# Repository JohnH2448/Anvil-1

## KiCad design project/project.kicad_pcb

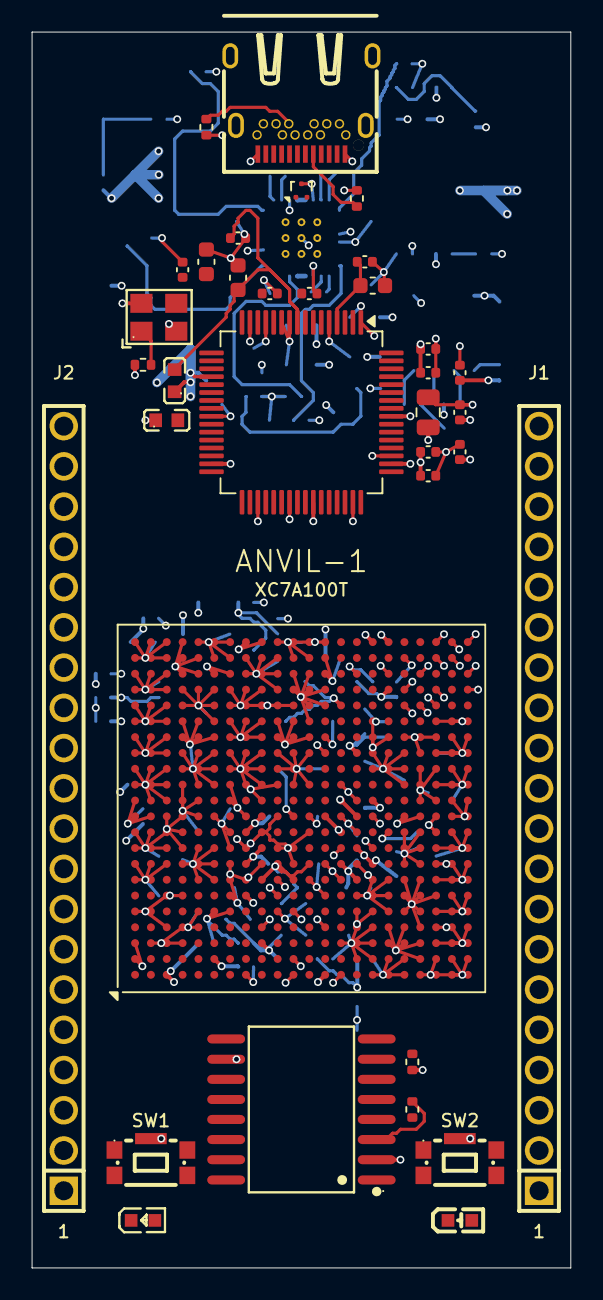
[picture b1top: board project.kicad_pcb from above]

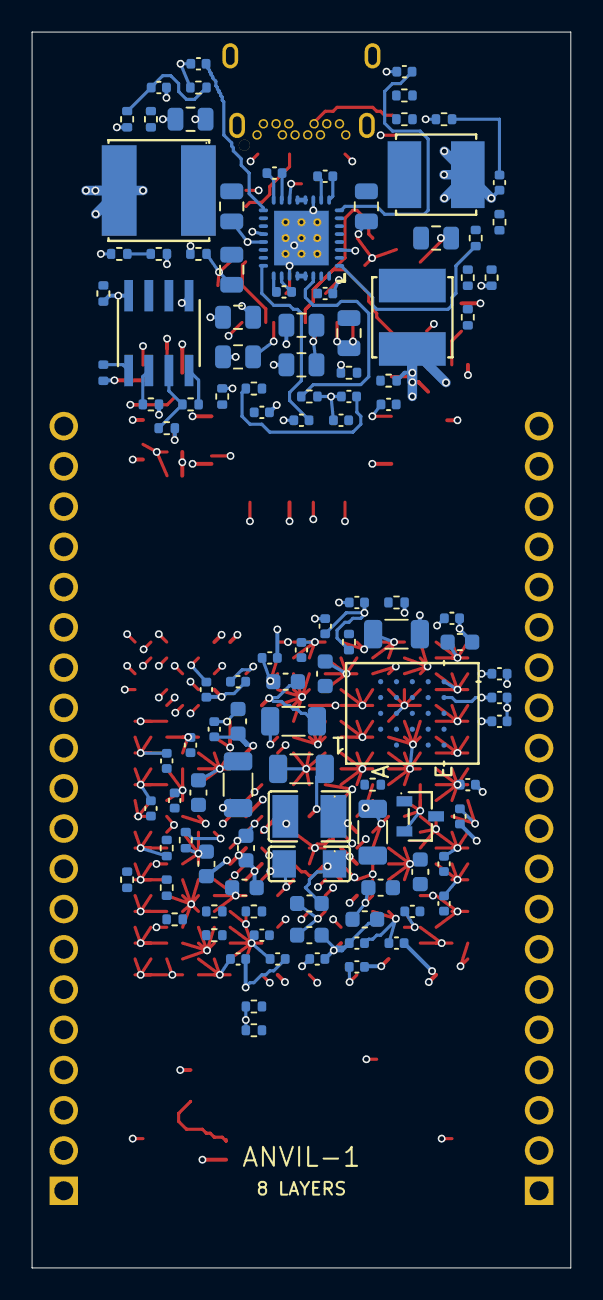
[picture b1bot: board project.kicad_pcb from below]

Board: 8 copper layers, 34.0 x 78.0 mm, 149 parts (114 on the bottom side), 120 nets.

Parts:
C1, C11, C16: 47nF; C_0402_1005Metric
C2, C3, C13, C15, C18, C20, C24: 22µF; C_0805_2012Metric
C4: 1.2nF; C_0402_1005Metric
C5, C14, C19: 22pF; C_0402_1005Metric
C6, C7, C8, C10: 10µF; C_0805_2012Metric
C9: 1µF; C_0402_1005Metric
C12, C17: 2.2nF; C_0402_1005Metric
C21, C22, C23, C27, C29, C31, C32, C33, C34, C35, C36, C37, C38, C39, C67, C76, C77, C78, C79: 100nF; C_0402_1005Metric
C25: 0.1µF; C_0402_1005Metric
C26: 3.3µF; C_0603_1608Metric
C28, C30, C41, C43, C44, C45, C46, C47, C58, C59, C65, C70, C72, C83, C85: 4.7µF; C_0603_1608Metric
C40: 330µF; C314600_C1210
C42, C48, C49, C50, C51, C52, C53, C54, C55, C60, C61, C62, C63, C64, C69, C73, C74, C75, C80, C81, C82, C84: 0.47µF; C_0402_1005Metric
C56: 0.47µF; C_1206_3216Metric
C57: 100µF; C15008_C1206
C66, C68, C71, C86: 47µF; C_1206_3216Metric
FB1, FB2: 600Ω@100MHz; C1002_L0603
J1, J2: 2.54mm 1*20P; C50981_HDR-TH_20P-P2_54-V-M-1
L1: 2.2µH; C160951_IND-SMD_L6_0-W6_0
L2, L3: 4.7µH; C162577_IND-SMD_L5_0-W5_0
LED1: GREEN; C2289_LED0603-RD
LED2: RED; C2286_LED-SMD_L1_6-W0_8-R-RD
OSC1: OT2EL89CJI-111YLC-12M; C5280582_OSC-SMD_4P-L3_2-W2_5-BL
Q1: AO3400A; C20917_SOT-23-3_L2_9-W1_3-P1_90-LS2_4-BR
R1, R7, R8, R11, R14, R19, R22, R25, R26, R27, R36, R39, R41, R42: 10kΩ; R_0402_1005Metric
R2: 12.4kΩ; R_0402_1005Metric
R3: 15kΩ; R_0402_1005Metric
R4: 73.2kΩ; R_0402_1005Metric
R5: 200kΩ; R_0402_1005Metric
R6: 67kΩ; R_0402_1005Metric
R9, R10: 20kΩ; R_0402_1005Metric
R12: 41.1kΩ; R_0402_1005Metric
R13: 45.3kΩ; R_0402_1005Metric
R15, R16, R17, R18: 100kΩ; R_0402_1005Metric
R20, R21: 5.1kΩ; R_0402_1005Metric
R23: 12kΩ; R_0402_1005Metric
R24, R40: 2.2kΩ; R_0402_1005Metric
R28, R29, R30, R31, R32, R34: 4.7kΩ; R_0402_1005Metric
R33, R37: 100Ω; R_0402_1005Metric
R35: 130Ω; R_0402_1005Metric
R38: 680Ω; R_0402_1005Metric
SW1, SW2: KMR221GLFS; C72443_KEY-SMD_KMR2XXGXXX
U1: XC7A100T-FGG484; BGA-484_23.0x23.0mm_Layout22x22_P1.0mm
U2: TPS65261RHBR; RHB0032E
U3: FT2232HL; LQFP-64_10x10mm_P0.5mm
U4: 93LC46B-E/SN; SOIC8-N_MC_MCH
U5: TPD2EUSB30; Texas_DRT-3
U6: W25Q256JVFIQT; C779876_SOIC-16_L10_3-W7_5-P1_27-LS10_3-BL
U7: IS66WVH16M8DALL-166B1LI; BGA24_IS66_ISI
USB1: USB-306F; C309341_USB-TYPE-C-TH_USB-306K

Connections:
/FPGA_CK_N: U1.E3, U7.B1
/FPGA_CK_P: U1.F3, U7.B2
/FPGA_CS: R41.2, U1.F1, U7.A3
/FPGA_RESET: R42.2, U1.K1, U7.A4
/FPGA_RWDS: R40.2, U1.H4, U7.C3
/FTDI_JTAG_TCK: U1.V12, U3.16
/FTDI_JTAG_TDI: U1.R13, U3.17
/FTDI_JTAG_TDO: U1.U13, U3.18
/FTDI_JTAG_TMS: U1.T13, U3.19
/OSC_12: OSC1.3, U1.W19, U3.2
/SPI_CLK: U1.L12, U6.16
/SPI_CS: R28.2, U1.T19, U6.7
/SPI_IO0: U1.P22, U6.15
/SPI_IO1: U1.R22, U6.8
/SPI_IO2: U1.P21, U6.9
/SPI_IO3: U1.R21, U6.1
/UART_RX: U1.R17, U3.38
/UART_TX: U1.N15, U3.39
/VBUS: C6.2, C7.2, C8.2, C9.2, R5.1, U2.12, U2.13, U2.28, U2.29, USB1.A4, USB1.A9, USB1.B4, USB1.B9
FTDI_VREGOUT: C26.1, C33.1, C34.1, C35.1, U3.12, U3.37, U3.49, U3.64
GND: C2.1, C3.1, C4.2, C6.1, C7.1, C8.1, C9.1, C10.1, C12.2, C13.1, C15.1, C17.2, C18.1, C20.1, C21.2, C22.2, C23.2, C24.2, C25.2, C26.2, C27.2, C28.2, C29.2, C30.2, C31.2, C32.2, C33.2, C34.2, C35.2, C36.2, C37.2, C38.2, C39.2, C40.2, C41.2, C42.2, C43.2, C44.2, C45.2, C46.2, C47.2, C48.2, C49.2, C50.2, C51.2, C52.2, C53.2, C54.2, C55.2, C56.2, C57.2, C58.2, C59.2, C60.2, C61.2, C62.2, C63.2, C64.2, C65.2, C66.2, C67.1, C68.2, C69.2, C70.2, C71.2, C72.2, C73.2, C74.2, C75.2, C76.2, C77.1, C78.1, C79.2, C80.2, C81.2, C82.2, C83.2, C84.2, C85.2, C86.2, J1.5, J1.10, J1.15, J1.20, J2.5, J2.10, J2.15, J2.20, OSC1.2, Q1.2, R3.2, R4.1, R6.1, R11.2, R14.2, R20.1, R21.2, R23.2, R30.1, R31.1, R33.2, R37.2, SW1.5, SW2.5, U1.A2, U1.A3, U1.A5, U1.A7, U1.A8, U1.A9, U1.A10, U1.A11, U1.A12, U1.A13, U1.A14, U1.A15, U1.A16, U1.A17, U1.A18, U1.A19, U1.A20, U1.A21, U1.A22, U1.AA1, U1.AA2, U1.AA3, U1.AA4, U1.AA5, U1.AA6, U1.AA7, U1.AA8, U1.AA9, U1.AA10, U1.AA11, U1.AA12, U1.AA13, U1.AA14, U1.AA15, U1.AA16, U1.AA17, U1.AA22, U1.AB1, U1.AB2, U1.AB3, U1.AB4, U1.AB5, U1.AB6, U1.AB7, U1.AB8, U1.AB9, U1.AB10, U1.AB11, U1.AB12, U1.AB13, U1.AB14, U1.AB15, U1.AB16, U1.AB17, U1.AB19, U1.B3, U1.B5, U1.B7, U1.B8, U1.B9, U1.B10, U1.B11, U1.B12, U1.B13, U1.B14, U1.B15, U1.B16, U1.B17, U1.B18, U1.B19, U1.B20, U1.B21, U1.B22, U1.C3, U1.C4, U1.C6, U1.C8, U1.C9, U1.C10, U1.C11, U1.C12, U1.C13, U1.C14, U1.C15, U1.C16, U1.C17, U1.C18, U1.C19, U1.C20, U1.C21, U1.C22, U1.D3, U1.D4, U1.D6, U1.D8, U1.D9, U1.D10, U1.D11, U1.D12, U1.D13, U1.D14, U1.D15, U1.D16, U1.D17, U1.D18, U1.D19, U1.D20, U1.D21, U1.D22, U1.E4, U1.E5, U1.E7, U1.E8, U1.E9, U1.E11, U1.E12, U1.E13, U1.E14, U1.E15, U1.E16, U1.E17, U1.E18, U1.E19, U1.E20, U1.E21, U1.E22, U1.F5, U1.F7, U1.F8, U1.F9, U1.F11, U1.F13, U1.F14, U1.F15, U1.F16, U1.F17, U1.F18, U1.F19, U1.F20, U1.F21, U1.F22, U1.G5, U1.G6, U1.G7, U1.G8, U1.G9, U1.G10, U1.G12, U1.G13, U1.G14, U1.G15, U1.G16, U1.G17, U1.G18, U1.G19, U1.G20, U1.G21, U1.G22, U1.H1, U1.H7, U1.H9, U1.H11, U1.H13, U1.H14, U1.H15, U1.H16, U1.H17, U1.H18, U1.H19, U1.H20, U1.H21, U1.H22, U1.J8, U1.J10, U1.J12, U1.J13, U1.J14, U1.J15, U1.J16, U1.J17, U1.J18, U1.J19, U1.J20, U1.J21, U1.J22, U1.K5, U1.K7, U1.K9, U1.K11, U1.K13, U1.K14, U1.K15, U1.K16, U1.K17, U1.K18, U1.K19, U1.K20, U1.K21, U1.K22, U1.L2, U1.L8, U1.L9, U1.L13, U1.L14, U1.L15, U1.L16, U1.L17, U1.L18, U1.L19, U1.L20, U1.L21, U1.L22, U1.M7, U1.M10, U1.M11, U1.M13, U1.M15, U1.M16, U1.M17, U1.M18, U1.M19, U1.M20, U1.M21, U1.M22, U1.N6, U1.N8, U1.N16, U1.N18, U1.N19, U1.N20, U1.N21, U1.N22, U1.P3, U1.P7, U1.P9, U1.P11, U1.P13, U1.R2, U1.R3, U1.R4, U1.R5, U1.R6, U1.R8, U1.R10, U1.R12, U1.R20, U1.T1, U1.T2, U1.T3, U1.T4, U1.T5, U1.T6, U1.T7, U1.T9, U1.T11, U1.T14, U1.T15, U1.T16, U1.T17, U1.U1, U1.U2, U1.U3, U1.U4, U1.U5, U1.U6, U1.U7, U1.U14, U1.U15, U1.U16, U1.V1, U1.V2, U1.V3, U1.V4, U1.V5, U1.V6, U1.V7, U1.V8, U1.V9, U1.V10, U1.V11, U1.V13, U1.V14, U1.V15, U1.V16, U1.V21, U1.W1, U1.W2, U1.W3, U1.W4, U1.W5, U1.W6, U1.W7, U1.W8, U1.W9, U1.W10, U1.W11, U1.W12, U1.W13, U1.W14, U1.W15, U1.W16, U1.W18, U1.Y1, U1.Y2, U1.Y3, U1.Y4, U1.Y5, U1.Y6, U1.Y7, U1.Y8, U1.Y9, U1.Y10, U1.Y11, U1.Y12, U1.Y13, U1.Y14, U1.Y15, U1.Y16, U1.Y17, U2.11, U2.14, U2.21, U2.27, U2.33, U3.1, U3.5, U3.10, U3.11, U3.13, U3.15, U3.25, U3.35, U3.47, U3.51, U4.5, U5.3, U6.10, U7.B3, U7.C1, U7.E5, USB1.25, USB1.A1, USB1.A12, USB1.B1, USB1.B12
unnamed: C4.1, R2.2
unnamed: C12.1, R9.2
unnamed: C17.1, R12.2
unnamed: LED1.2, R35.2
unnamed: LED1.1, Q1.3
unnamed: LED2.1, R38.1
unnamed: LED2.2, R8.2, U2.2
unnamed: OSC1.1, R19.2
unnamed: Q1.1, U1.G11
unnamed: R32.1, SW2.2
unnamed: R33.1, SW2.4
unnamed: R36.1, SW1.2
unnamed: R37.1, SW1.4
unnamed: J1.2, U1.AA21
unnamed: J1.1, U1.AA20
unnamed: J1.4, U1.Y22
unnamed: J1.3, U1.Y21
unnamed: J1.6, U1.AB22
unnamed: J1.8, U1.V20
unnamed: J1.7, U1.U20
unnamed: J1.9, U1.W20
unnamed: J1.12, U1.Y19
unnamed: J1.11, U1.Y18
unnamed: J1.14, U1.V19
unnamed: J1.13, U1.V18
unnamed: J1.16, U1.AB20
unnamed: J1.18, U1.W17
unnamed: J1.17, U1.V17
unnamed: J1.19, U1.AA18
unnamed: SW1.1, U1.U17
unnamed: U1.F4, U7.E3
unnamed: U1.A1, U7.E1
unnamed: U1.B1, U7.E2
unnamed: U1.B2, U7.D4
unnamed: U1.C2, U7.D5
unnamed: U1.D1, U7.D2
unnamed: U1.E1, U7.D3
unnamed: U1.G1, U7.C4
unnamed: R40.1, U1.G3
unnamed: J2.2, U1.J4
unnamed: J2.1, U1.K4
unnamed: J2.4, U1.K3
unnamed: J2.3, U1.L3
unnamed: J2.6, U1.L1
unnamed: J2.8, U1.M2
unnamed: J2.7, U1.M3
unnamed: J2.9, U1.K6
unnamed: J2.12, U1.L4
unnamed: J2.11, U1.L5
unnamed: J2.14, U1.N3
unnamed: J2.13, U1.N4
unnamed: J2.16, U1.P1
unnamed: J2.18, U1.P4
unnamed: J2.17, U1.P5
unnamed: J2.19, U1.P2
unnamed: R34.2, U1.U12
unnamed: R29.2, U1.U11
unnamed: R30.2, U1.U10
unnamed: R31.2, U1.U9
unnamed: SW2.1, U1.N12
unnamed: C1.1, U2.25
unnamed: C11.1, U2.9
unnamed: C16.1, U2.16
unnamed: R2.1, U2.23
unnamed: R9.1, U2.7
unnamed: R12.1, U2.18
unnamed: R15.1, U2.31
unnamed: R16.1, U2.32
unnamed: R17.1, U2.1
unnamed: C5.2, R1.2, R3.1, U2.22
unnamed: C14.2, R10.2, R11.1, U2.6
unnamed: C19.2, R13.2, R14.1, U2.19
unnamed: C1.2, L1.1, U2.26
unnamed: C11.2, L2.1, U2.10
unnamed: C16.2, L3.1, U2.15
unnamed: R18.1, U2.4
unnamed: R7.2, U2.3
unnamed: R4.2, U2.20
unnamed: C23.1, U2.24
unnamed: C22.1, U2.8
unnamed: C21.1, U2.17
unnamed: R5.2, R6.2, U2.30
unnamed: R26.2, U3.62, U4.2
unnamed: R25.2, U3.63, U4.1
unnamed: R24.2, R27.2, U3.61, U4.3
unnamed: R23.1, U3.6
unnamed: C30.1, C31.1, FB2.2, U3.4
unnamed: C28.1, C29.1, FB1.2, U3.9
unnamed: R22.2, U3.14
unnamed: R24.1, U4.4
unnamed: R39.2, U6.3
unnamed: R21.1, USB1.A5
unnamed: R20.2, USB1.B5
USB_DN: U3.7, U5.2, USB1.A7, USB1.B7
USB_DP: U3.8, U5.1, USB1.A6, USB1.B6
V7V: C10.2, R15.2, R16.2, R17.2, R18.2, U2.5
VCC1V0: C2.2, C3.2, C5.1, C40.1, C41.1, C42.1, C43.1, C44.1, C45.1, C46.1, C47.1, C48.1, C49.1, C50.1, C51.1, C52.1, C53.1, C54.1, C55.1, C56.1, C57.1, L1.2, R1.1, U1.H8, U1.H10, U1.J7, U1.J9, U1.J11, U1.K8, U1.L7, U1.L11, U1.M8, U1.N7, U1.N11, U1.P8, U1.P10, U1.R7, U1.R9, U1.T8, U1.T10
VCC1V8: C13.2, C14.1, C15.2, C58.1, C59.1, C60.1, C61.1, C62.1, C63.1, C64.1, C65.1, C66.1, C67.2, C77.2, C78.2, C79.1, C80.1, C81.1, C82.1, C83.1, C84.1, C85.1, C86.1, L2.2, R10.1, R41.1, R42.1, U1.C1, U1.F2, U1.H6, U1.H12, U1.J3, U1.K10, U1.K12, U1.M4, U1.M12, U1.N1, U1.P12, U1.R11, U7.B4, U7.D1, U7.E4
VCC3V3: C18.2, C19.1, C20.2, C24.1, C25.1, C27.1, C32.1, C36.1, C37.1, C38.1, C39.1, C68.1, C69.1, C70.1, C71.1, C72.1, C73.1, C74.1, C75.1, C76.1, FB1.1, FB2.1, L3.2, OSC1.4, R7.1, R8.1, R13.1, R19.1, R22.1, R25.1, R26.1, R27.1, R28.1, R29.1, R32.2, R34.1, R35.1, R36.2, R38.2, R39.1, U1.F12, U1.M14, U1.P18, U1.R15, U1.T12, U1.T22, U1.U8, U1.U19, U1.U22, U1.Y20, U3.20, U3.31, U3.42, U3.50, U3.56, U4.8, U6.2
